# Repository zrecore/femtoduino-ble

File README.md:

femtoduino-ble
==============

The Smallest Arduino compatible board, with onboard Bluetooth 4.0 (BLE)

The sample sketch(es) and Android application(s) are available within the Arduino/ and Android/ folders, respectively.

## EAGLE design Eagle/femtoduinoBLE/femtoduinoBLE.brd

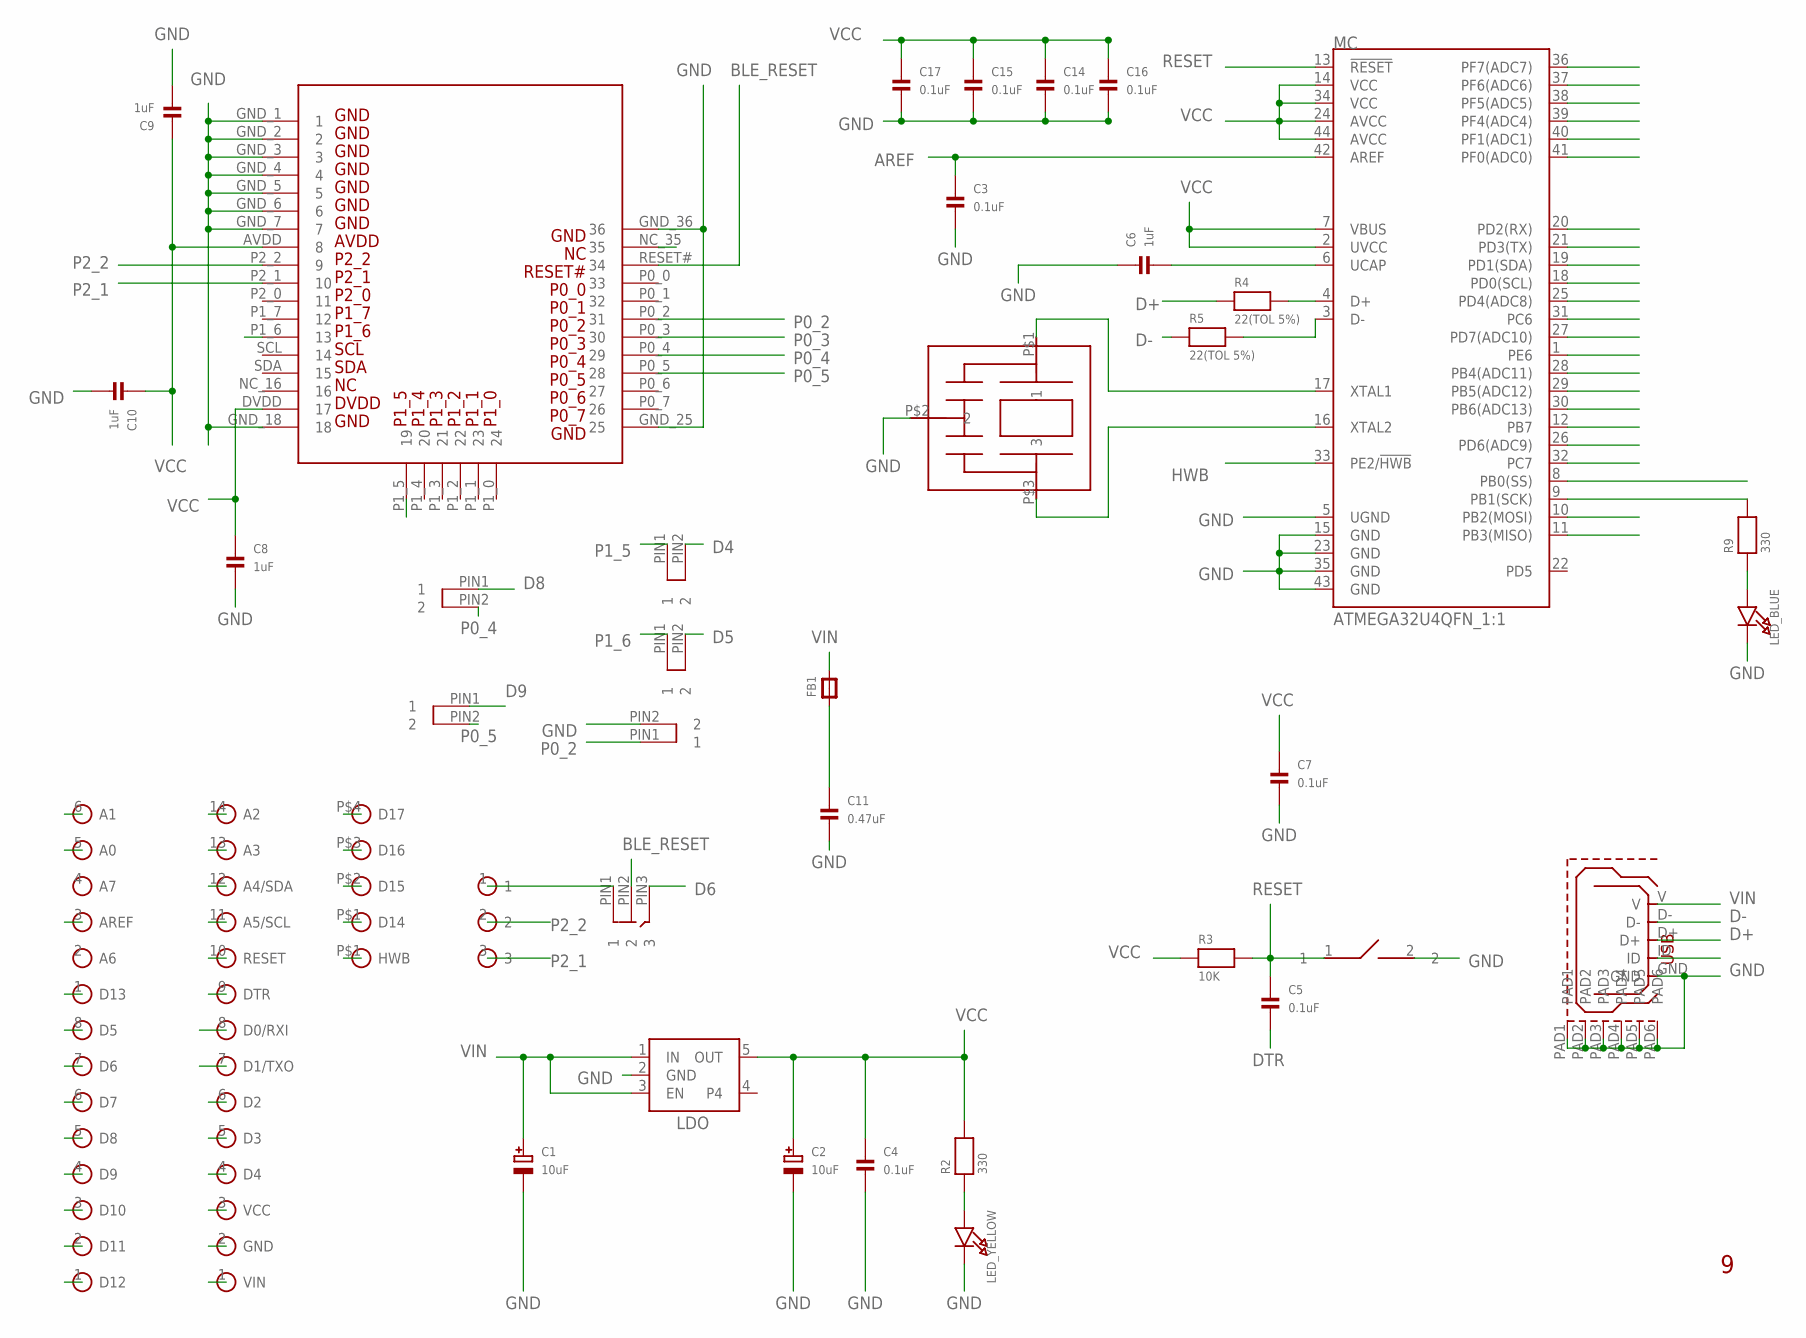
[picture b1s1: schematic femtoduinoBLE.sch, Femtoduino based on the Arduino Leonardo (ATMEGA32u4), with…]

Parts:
BLE_CTS: DNP; SPST_SMD_BRIDGED
C1, C2: 10uF; EIA3216-18/A-R
C3, C4, C5, C7, C14, C15, C16, C17: 0.1uF; _0402
C6: 1uF; _0402
C8, C9, C10: 1uF; 0402
C11: 0.47uF; _0402
FB1: FERRITE; 0603
LED_BLUE: LED0603_NOOUTLINE; CHIPLED_0603_NOOUTLINE
LED_YELLOW: LED0603_NOOUTLINE; CHIPLED_0603_NOOUTLINE
MC: ATMEGA32U4QFN_1:1; QFN-44-NOPAD_1:1
R2, R9: 330; _0402
R3: 10K; _0402
R4, R5: 22(TOL 5%); 0402
U$1: USB_MICROB; USB_MICROB_PACKAGE
U$2: CSTCE16MOV51-RO; CSTCE16M0V51-RO_PACKAGE
U$4: LDO_REGULATOR
U$5: 05_PINHEAD_1X6; 05_PINHEAD_1X6_PACKAGE
U$6: 05_PINHEAD_1X8; 05_PINHEAD_1X8_PACKAGE
U$7: 05_PINHEAD_1X14; 05_PINHEAD_1X14_PACKAGE
U$9: DNP; SPST_SMD
U$10: 05_PINHEAD_1X4; 05_PINHEAD_1X4_PACKAGE
U$11: 05_PINHEAD_1X1; 05_PINHEAD_1X1_PACKAGE
U$12: BLE113-A
U$13, U$14, U$15, U$16: DNP; SPST_SMD_BRIDGED
U$19: DNP; SPST_3_SMD
U$20: 05_PINHEAD_HEADER_1X3; 05_PINHEAD_1X3_HEAD_PACKAGE

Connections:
A0: MC.36 (PF7(ADC7)), U$5.5 (A0)
A1: MC.37 (PF6(ADC6)), U$5.6 (A1)
A2: MC.38 (PF5(ADC5)), U$7.14 (A2)
A3: MC.39 (PF4(ADC4)), U$7.13 (A3)
A4: MC.40 (PF1(ADC1)), U$7.12 (A4/SDA)
A5: MC.41 (PF0(ADC0)), U$7.11 (A5/SCL)
AREF: C3.1, MC.42 (AREF), U$5.3 (AREF)
BLE_RESET: U$12.RESET# (34), U$19.PIN2 (2)
D2: MC.19 (PD1(SDA)), U$7.6 (D2)
D3: MC.18 (PD0(SCL)), U$7.5 (D3)
D4: MC.25 (PD4(ADC8)), U$7.4 (D4), U$16.PIN2 (2)
D5: MC.31 (PC6), U$6.8 (D5), U$15.PIN2 (2)
D6: MC.27 (PD7(ADC10)), U$6.7 (D6), U$19.PIN3 (3)
D7: MC.1 (PE6), U$6.6 (D7)
D8: MC.28 (PB4(ADC11)), U$6.5 (D8), U$13.PIN1 (1)
D9: MC.29 (PB5(ADC12)), U$6.4 (D9), U$14.PIN1 (1)
D10: MC.30 (PB6(ADC13)), U$6.3 (D10)
D11: MC.12 (PB7), U$6.2 (D11)
D12: MC.26 (PD6(ADC9)), U$6.1 (D12)
D13: MC.32 (PC7), U$5.1 (D13)
D14: MC.11 (PB3(MISO)), U$10.P$1 (D14)
D15: MC.9 (PB1(SCK)), R9.2, U$10.P$2 (D15)
D16: MC.10 (PB2(MOSI)), U$10.P$3 (D16)
D17: MC.8 (PB0(SS)), U$10.P$4 (D17)
D+: R4.1, U$1.D+
D-: R5.1, U$1.D-
DTR: C5.2, U$7.9 (DTR)
GND: BLE_CTS.PIN2 (2), C1.-, C2.-, C3.2, C4.2, C6.1, C7.2, C8.2, C9.2, C10.2, C11.2, C14.2, C15.2, C16.2, C17.2, LED_BLUE.C, LED_YELLOW.C, MC.5 (UGND), MC.15 (GND), MC.23 (GND), MC.35 (GND), MC.43 (GND), U$1.GND, U$1.PAD1, U$1.PAD2, U$1.PAD3, U$1.PAD4, U$1.PAD5, U$1.PAD6, U$2.P$2 (2), U$4.2 (GND), U$7.2 (GND), U$9.2, U$12.GND_1 (1), U$12.GND_2 (2), U$12.GND_3 (3), U$12.GND_4 (4), U$12.GND_5 (5), U$12.GND_6 (6), U$12.GND_7 (7), U$12.GND_18 (18), U$12.GND_25 (25), U$12.GND_36 (36)
HWB: MC.33 (PE2/!HWB), U$11.P$1
unnamed: C11.1, FB1.1
unnamed: LED_BLUE.A, R9.1
unnamed: LED_YELLOW.A, R2.1
unnamed: U$19.PIN1 (1), U$20.1
unnamed: MC.4 (D+), R4.2
unnamed: MC.3 (D-), R5.2
P0_2: BLE_CTS.PIN1 (1), U$12.P0_2 (31)
P0_3: U$12.P0_3 (30)
P0_4: U$12.P0_4 (29), U$13.PIN2 (2)
P0_5: U$12.P0_5 (28), U$14.PIN2 (2)
P1_5: U$12.P1_5 (19), U$16.PIN1 (1)
P1_6: U$12.P1_6 (13), U$15.PIN1 (1)
P2_1: U$12.P2_1 (10), U$20.3
P2_2: U$12.P2_2 (9), U$20.2
RESET: C5.1, MC.13 (!RESET), R3.2, U$7.10 (RESET), U$9.1
RXI: MC.20 (PD2(RX)), U$7.8 (D0/RXI)
TXO: MC.21 (PD3(TX)), U$7.7 (D1/TXO)
UCAP: C6.2, MC.6 (UCAP)
VCC: C2.+, C4.1, C7.1, C8.1, C9.1, C10.1, C14.1, C15.1, C16.1, C17.1, MC.2 (UVCC), MC.7 (VBUS), MC.14 (VCC), MC.24 (AVCC), MC.34 (VCC), MC.44 (AVCC), R2.2, R3.1, U$4.5 (OUT), U$7.3 (VCC), U$12.AVDD (8), U$12.DVDD (17)
VIN: C1.+, FB1.2, U$1.V, U$4.1 (IN), U$4.3 (EN), U$7.1 (VIN)
XTAL1: MC.17 (XTAL1), U$2.P$1 (1)
XTAL2: MC.16 (XTAL2), U$2.P$3 (3)

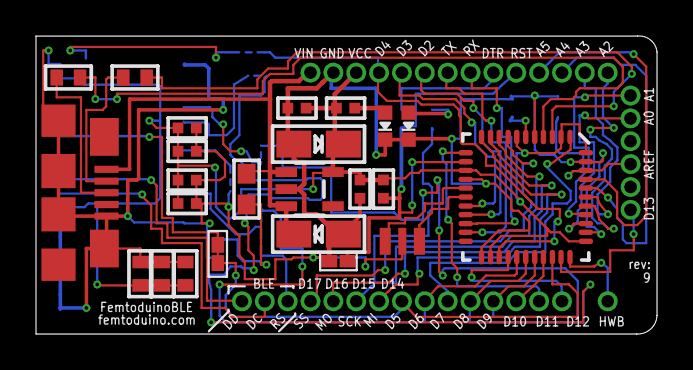
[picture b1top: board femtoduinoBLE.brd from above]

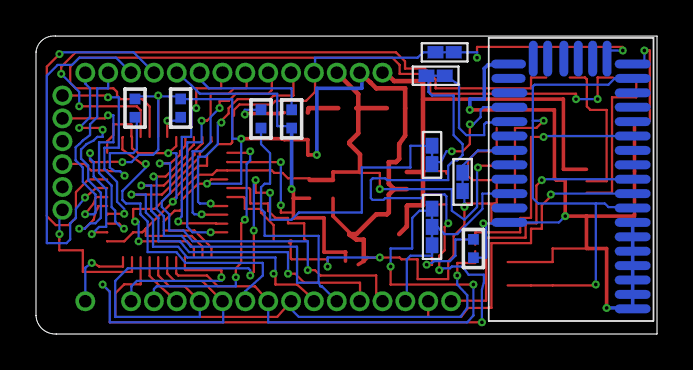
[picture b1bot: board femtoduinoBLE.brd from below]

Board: 4 copper layers, 34.5 x 16.6 mm, 41 parts (11 on the bottom side), 50 nets.

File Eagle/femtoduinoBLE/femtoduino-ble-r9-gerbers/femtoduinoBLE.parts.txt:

Partlist

Exported from femtoduinoBLE.brd at 5/10/14 7:51 PM

EAGLE Version 6.5.0 Copyright (c) 1988-2013 CadSoft

Assembly variant: 

Part       Value                 Package                     Position (mm)         Orientation

C1         10uF                  1206                        (15.7 5.6)            R180
C2         10uF                  1206                        (15.7 10.6)           R0
C3         0.1uF                 0402                        (29 12.6)             MR90
C4         0.1uF                 0402                        (14.5 12.6)           R180
C5         0.1uF                 0402                        (20.3 12)             MR90
C6         1uF                   0402                        (26.4668 12.6)        MR270
C7         0.1uF                 0402                        (18 8.1)              R270
C8         1uF                   0402                        (5.8 3.4)             R90
C9         1uF                   0402                        (7 3.4)               R90
C10        1uF                   0402                        (8.3 3.4)             R90
C11        0.47uF                0402                        (10.2 4.8)            MR270
C14        0.1uF                 0402                        (8.4 7.3)             R0
C15        0.1uF                 0402                        (8.4 8.6)             R0
C16        0.1uF                 0402                        (8.4 10.2)            R0
C17        0.1uF                 0402                        (8.4 11.5)            R0
FB1        1K OHM                0603                        (11.7 8.1)            R90
LED_BLUE   Blue                  0603                        (20.7 11.6)           R180
LED_YELLOW Yellow                0603                        (19.4 11.6)           R180
MC         ATMEGA32U4QFN_1:1     QFN-44 (QFN-EP)             (27.21 7.66)          R270
R2         330                   0402                        (17.2 12.6)           R180
R3         10K                   0402                        (19.3 8.1)            R270
R4         22(TOL 5%)            0402                        (1.8 14.3)            R0
R5         22(TOL 5%)            0402                        (5.5 14.3)            R0
R9         330                   0402                        (22 12)               MR270
U$1        USB_MICROB            USB_MICROB_PACKAGE          (4.6 7.9)             R270
U$2        16MHz                 CSTCE16M0V51-RO_PACKAGE     (19.4 5.2)            R270
U$4        3V3                   LDO_REGULATOR               (15.2 8.1)            R270
U$12       BLE113-A              BLE113-A                    (0.2 16.5)            MR180

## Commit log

2014-02-25 Adding Arduino and Android code
2014-03-30 Updating to use latest BGLib headers (Feb 13, 2014 release)
2014-07-23 EAGLE PCB schematics and board files, BoM and parts

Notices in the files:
parts and their libraries:
SparkFun-DigitalIC: Licensing: CC v3.0 Share-Alike You are welcome to use this library for commercial purposes.
microbuilder: This work is placed in the public domain, and may be freely used for commercial and non-commercial work with the following conditions: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
